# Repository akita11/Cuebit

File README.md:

# Cue:bit

ライントレースと3色のカラーマーカでの動作制御ができるプログラミング教材ロボットカーです。micro:bitを装着して、micro:bitのカスタムブロックで動作制御することもできます。

[使い方・動作の例(YouTube動画)](https://youtu.be/czKjS_mCOlM)

## 使い方（ライントレースモード）

電源を入れると、ライントレースを開始します。また途中にカラーマーカーがあると、それに応じた動作をします。なおライン（黒）やカラーマーカを見失って0,5秒程度経過すると、自動的に停止します（本体LEDが黄色点灯）。ラインやマーカのあるところに移動させると、動作を再開します。

### カラーマーカーと動作の定義

赤・緑・黄の3色のマーカを3つ連続して配置されたところを通過すると、その色パターンに応じた動作を行います。色マーカは10mm程度の「丸ポチシール」（DAISOなどで売っているもの）や、同等の色を印刷したものを使います。(赤=R／緑=G／黄=Y）

- 緑-赤-黄 (GRY) : 速度を超ゆっくりに
- 赤-緑-黄 (RGY) : 速度をゆっくりに
- 赤-緑-赤 (RGR) : 速度を通常に
- 黄-緑-赤 (YGR) : 速度を速く
- 黄-赤-緑 (YRG) : 速度を超速く
- 黄-赤-黄 (YRY) : 一時停止（3秒程度）
- 緑-黄-赤 (GYR) : 次の交差点を左に90度曲がる
- 黄-緑-黄 (YGY) : 次の交差点を直進する
- 緑-黄-緑 (GYG) : 次の交差点を右に90度曲がる
- 赤-黄-赤 (RYR) : Uターンする
- 緑-赤-緑 (GRG) : バックする

## 使い方（micro:bitモード）

micro:bitのカスタムブロックを使ってCue:bitの動作を制御でききます。
[こちらの手順](https://docs.google.com/document/d/1bRiQpdVX2RdSoQZLEZQx14lWcuVc2Sd8CT0sPL3RYwU/)でMakeCode用カスタムブロックを追加し、micro:bitのプログラムを作成してmicro:bitに書き込みます。その後、そのmicro:bitをCue:bitに差し込んでCue:bitの電源をいれると、そのプログラム通りにCue:bitが動作します。

※モータの特性仕様上、左右の回転速度には差があり、以下のコマンドである程度は調整はできますが、完全に直進したり正確に指定距離だけ進む・回転することはできません。ご了承ください。

### 参考：技術的仕様

micro:bitからCue:bitへのコマンド（通信プロトコル:UART 9600bps N81）は以下です。以下の"NNN"は数値(10進数)で与えるコマンドパラメータです。また各コマンドは行末コード(0x0d or 0x0a)で終端します。なおCue:bitのGroveコネクタと本体後部の6ピンコネクタ用端子(FTDI-Basic用)も、micro:bitの通信端子と並列に接続されています。なお[「Groveケーブル-USBシリアル接続ケーブル」](https://www.switch-science.com/products/9460)を使うと、FTDI-Basicと本体Grove端子とを接続できます。なおソースコードはArduinoIDE等で書き込むことができます。（ターゲットはProMini(ATmega328P, 3.3V/8MHz)。新品ATmega328Pではこれ用のブートローダを書き込む必要あり）

- $ : micro:bit制御モードに開始
- \# : micro:bit制御モードを終了
- RNNN : NNN度回転（NNNが正=時計回り、負=反時計回り）（※実際の回転角度はモータ特性のばらつきなどから多少の誤差があります）
- B : 停止
- FNNN : NNN[cm]進む（※実際の移動距離はモータ特性のばらつきなどから多少の誤差があります）
- ZNNN : ジグザグ走行（およそNNN[cm]）
- SNNN : スケート走行（およそNNN[cm]）

以下はデバッグ用のコマンド

- P : パラメータの表示
- T : ライントレースモードを開始
- t : ライントレースモードを終了して停止
- D : デバッグ情報の表示を開始（Dに続けてr/g/y/wを書くと、色センサの値を各色の学習用のCSV形式で出力）
- d : デバッグ表示の表示を停止
- kNNN : ライントレース制御のKpパラメータ（float型）
- KNNN : ライントレース制御のKdパラメータ（float型）
- vNNN : 通常走行時の速度（float型。モータ駆動のPWM比として与えるため、値の範囲は0.0〜1.0）
- rNNN : 左右モータの速度調整（PWMデューティー比）（float型）（左モータのPWM比×r=右モータのPWM比として計算するため、v×rが1.0以下となること）
- fNNN : 1cm進むための時間[単位は10ms]（※実際の移動距離はモータ特性のばらつきなどから多少の誤差があります）
- gNNN : 10度回転するための時間[単位は10ms]（※実際の回転角度はモータ特性のばらつきなどから多少の誤差があります）
- ! : 各種パラメータをEEPROMに保存（起動時に読み込まれる）

## Author

Junichi Akita (@akita11) / akita@ifdl.jp

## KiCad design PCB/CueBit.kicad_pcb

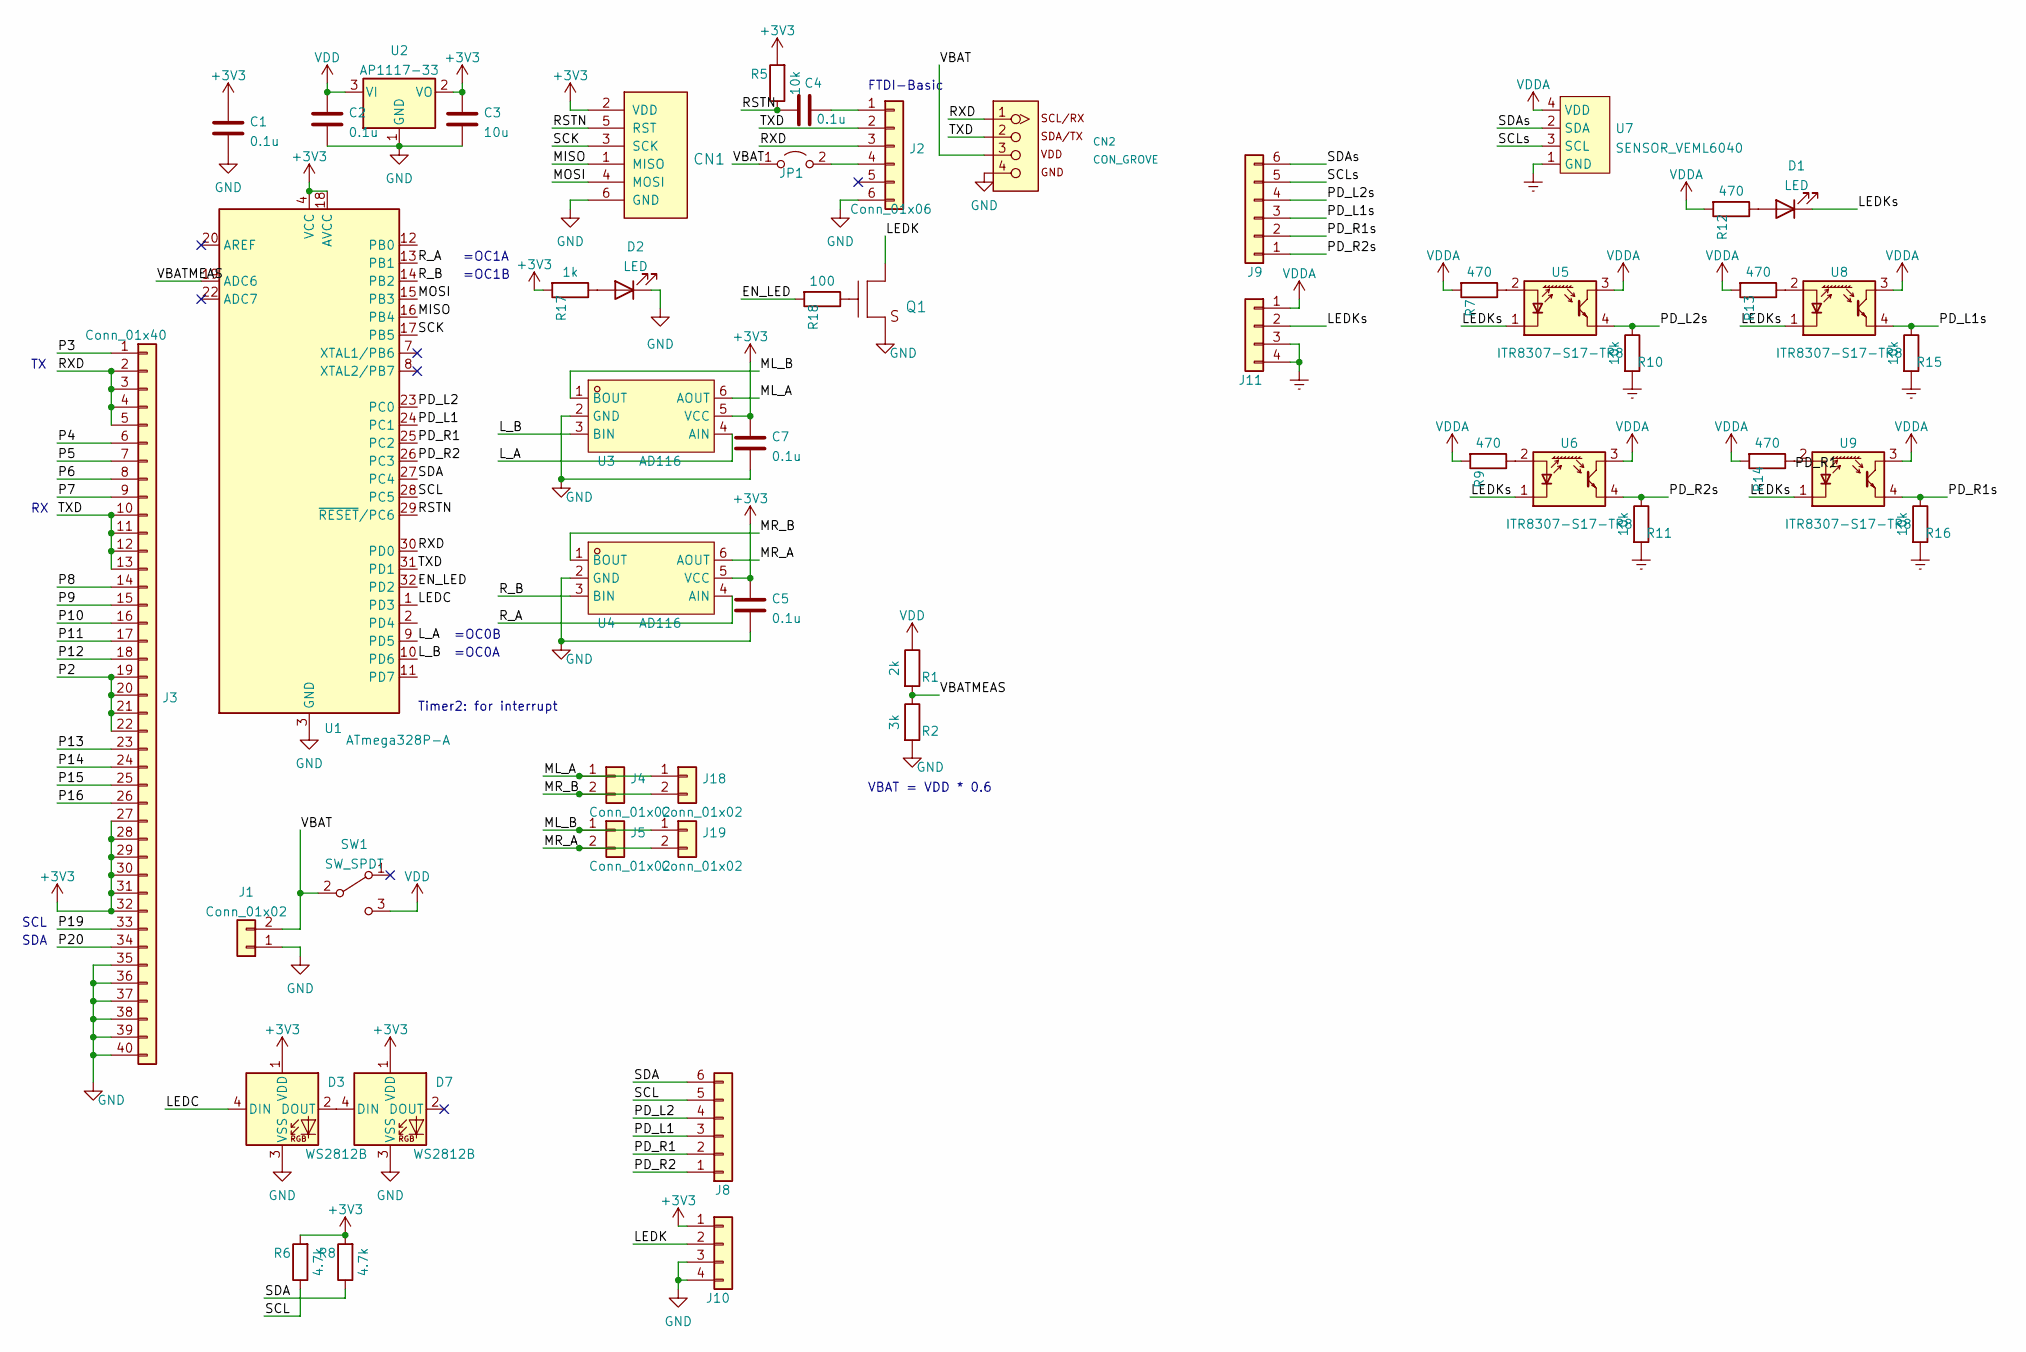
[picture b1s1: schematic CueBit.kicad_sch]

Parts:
C1, C2, C4, C5, C7: 0.1u; C_0603_1608Metric
C3: 10u; C_0603_1608Metric
CN1: CON_AVRISP; PinHeader_2x03_P2.54mm_Vertical
CN2: CON_GROVE; CON_GROVE_H_roundPad
D1, D2: LED; LED_0603_1608Metric
D3, D7: WS2812B; LED_WS2812B_PLCC4_5.0x5.0mm_P3.2mm
J1: Conn_01x02; JST_PH_B2B-PH-K_1x02_P2.00mm_Vertical
J2: Conn_01x06; PinSocket_1x06_P2.54mm_Vertical
J3: Conn_01x40; CON_microbit_cardedge_V_SMD
J4, J5: Conn_01x02; PinHeader_1x02_P2.54mm_Vertical
J8, J9: Conn_01x06; PinHeader_1x06_P2.54mm_Vertical
J10, J11: Conn_01x04; PinSocket_1x04_P2.54mm_Vertical
J18, J19: Conn_01x02; PinHeader_1x02_P2.54mm_Vertical_SMD_Pin1Right
JP1: Jumper_2_Open; SolderJumper-2_P1.3mm_Open_Pad1.0x1.5mm
Q1: TR_NMOS_IRLML6344; SOT-23
R1: 2k; R_0603_1608Metric; LCSC C2907022
R2: 3k; R_0603_1608Metric; LCSC C328357
R5, R10, R11, R15, R16: 10k; R_0603_1608Metric
R6, R8: 4.7k; R_0603_1608Metric
R7, R9, R12, R13, R14: 470; R_0603_1608Metric; LCSC C2907172
R17: 1k; R_0603_1608Metric
R18: 100; R_0603_1608Metric
SW1: SW_SPDT; SW_SK-12D11VG3
U1: ATmega328P-A; TQFP-32_7x7mm_P0.8mm; LCSC C14877
U2: AP1117-33; SOT-223-3_TabPin2; LCSC C2992570
U3, U4: AD116; SOT-23-6_L2.9-W1.6-P0.95-LS2.8-BL; LCSC Part C7463412
U5, U6, U8, U9: ITR8307-S17-TR8; Everlight_ITR1201SR10AR; LCSC C81632
U7: SENSOR_VEML6040; OPLGA-4; LCSC C78465

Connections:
+3V3: C1.1, C3.1, C5.1, C7.1, CN1.2 (VDD), D3.1 (VDD), D7.1 (VDD), J3.27, J3.28, J3.29, J3.30, J3.31, J3.32, J10.1, R5.2, R6.2, R8.2, R17.2, U1.4 (VCC), U1.6 (VCC), U1.18 (AVCC), U2.2 (VO), U3.5 (VCC), U4.5 (VCC)
/EN_LED: R18.2, U1.32 (PD2)
/LEDC: D3.4 (DIN), U1.1 (PD3)
/LEDK: J10.2, Q1.3 (D)
/LEDKs: D1.1 (K), J11.2, U5.1 (K), U6.1 (K), U8.1 (K), U9.1 (K)
/L_A: U1.9 (PD5), U3.4 (AIN)
/L_B: U1.10 (PD6), U3.3 (BIN)
/MISO: CN1.1 (MISO), U1.16 (PB4)
/ML_A: J4.1, J18.1, U3.6 (AOUT)
/ML_B: J5.1, J19.1, U3.1 (BOUT)
/MOSI: CN1.4 (MOSI), U1.15 (PB3)
/MR_A: J5.2, J19.2, U4.6 (AOUT)
/MR_B: J4.2, J18.2, U4.1 (BOUT)
/P2: J3.19, J3.20, J3.21, J3.22
/P3: J3.1
/P4: J3.6
/P5: J3.7
/P6: J3.8
/P7: J3.9
/P8: J3.14
/P9: J3.15
/P10: J3.16
/P11: J3.17
/P12: J3.18
/P13: J3.23
/P14: J3.24
/P15: J3.25
/P16: J3.26
/P19: J3.33
/P20: J3.34
/PD_L1: J8.3, U1.24 (PC1)
/PD_L1s: J9.3, R15.1, U8.4
/PD_L2: J8.4, U1.23 (PC0)
/PD_L2s: J9.4, R10.1, U5.4
/PD_R1: J8.2, U1.25 (PC2)
/PD_R1s: J9.2, R16.1, U9.4
/PD_R2: J8.1, U1.26 (PC3)
/PD_R2s: J9.1, R11.1, U6.4
/RSTN: C4.1, CN1.5 (RST), R5.1, U1.29 (~RESET/PC6)
/RXD: CN2.1, J2.3, J3.2, J3.3, J3.4, J3.5, U1.30 (PD0)
/R_A: U1.13 (PB1), U4.4 (AIN)
/R_B: U1.14 (PB2), U4.3 (BIN)
/SCK: CN1.3 (SCK), U1.17 (PB5)
/SCL: J8.5, R6.1, U1.28 (PC5)
/SCLs: J9.5, U7.3 (SCL)
/SDA: J8.6, R8.1, U1.27 (PC4)
/SDAs: J9.6, U7.2 (SDA)
/TXD: CN2.2, J2.2, J3.10, J3.11, J3.12, J3.13, U1.31 (PD1)
/VBAT: CN2.3, J1.2, JP1.1 (A), SW1.2 (B)
/VBATMEAS: R1.2, R2.1, U1.19 (ADC6)
Earth: J11.3, J11.4, R10.2, R11.2, R15.2, R16.2, U7.1 (GND)
GND: C1.2, C2.2, C3.2, C5.2, C7.2, CN1.6 (GND), CN2.4, D2.1 (K), D3.3 (VSS), D7.3 (VSS), J1.1, J2.6, J3.35, J3.36, J3.37, J3.38, J3.39, J3.40, J10.3, J10.4, Q1.2 (S), R2.2, U1.3 (GND), U1.5 (GND), U1.21 (GND), U2.1 (GND), U3.2 (GND), U4.2 (GND)
unnamed: C4.2, J2.1
unnamed: D1.2 (A), R12.1
unnamed: D2.2 (A), R17.1
unnamed: D3.2 (DOUT), D7.4 (DIN)
unnamed: J2.4, JP1.2 (B)
unnamed: Q1.1 (G), R18.1
unnamed: R7.1, U5.2 (A)
unnamed: R9.1, U6.2 (A)
unnamed: R13.1, U8.2 (A)
unnamed: R14.1, U9.2 (A)
VDD: C2.1, R1.1, SW1.3 (C), U2.3 (VI)
VDDA: J11.1, R7.2, R9.2, R12.2, R13.2, R14.2, U5.3, U6.3, U7.4 (VDD), U8.3, U9.3

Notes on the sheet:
SDA
VBAT = VDD * 0.6
Timer2: for interrupt
FTDI-Basic
=OC1A
=OC1B
=OC0B
=OC0A
SCL

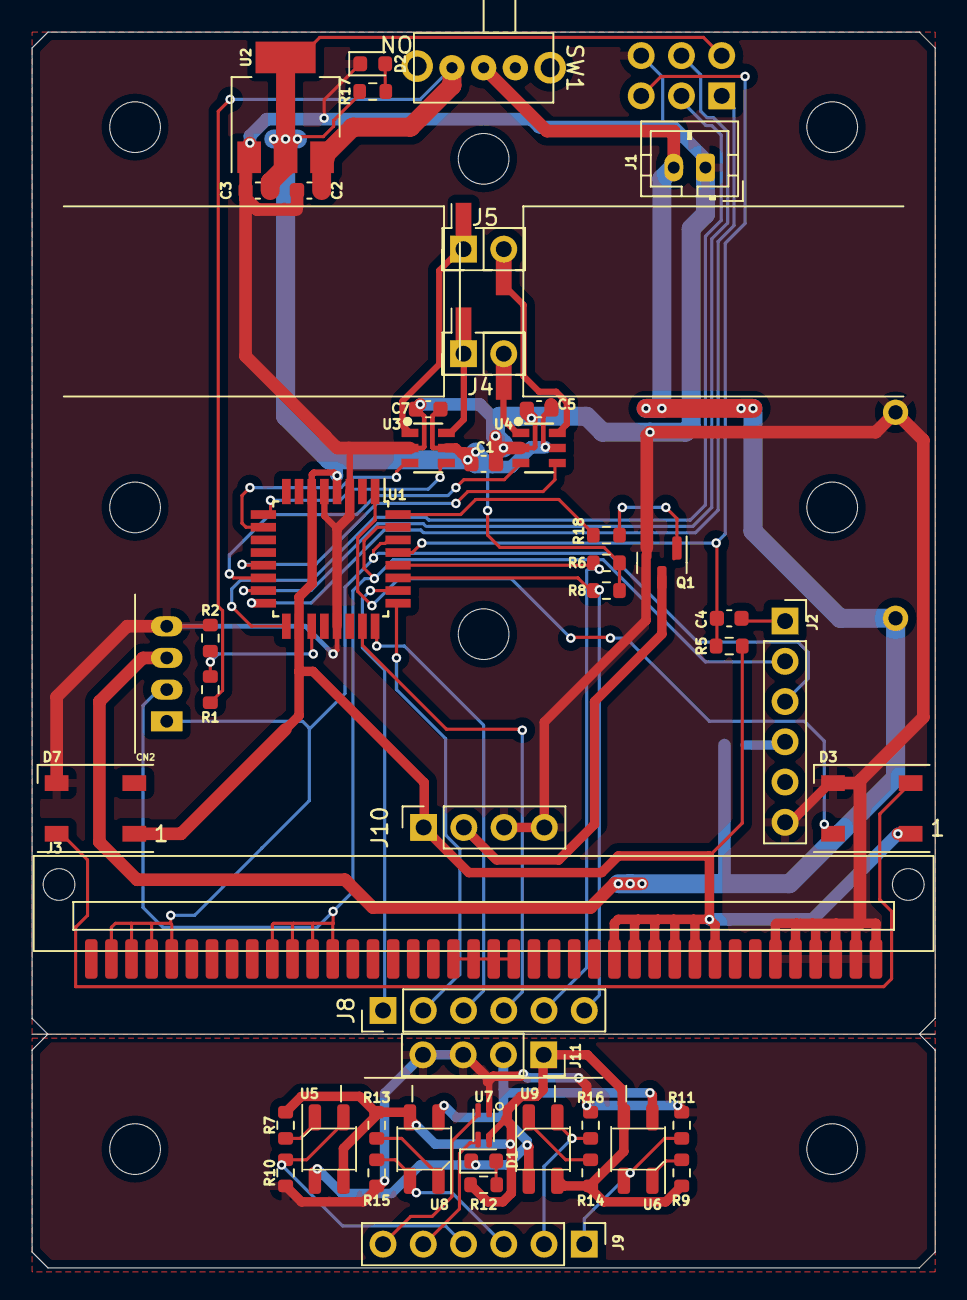
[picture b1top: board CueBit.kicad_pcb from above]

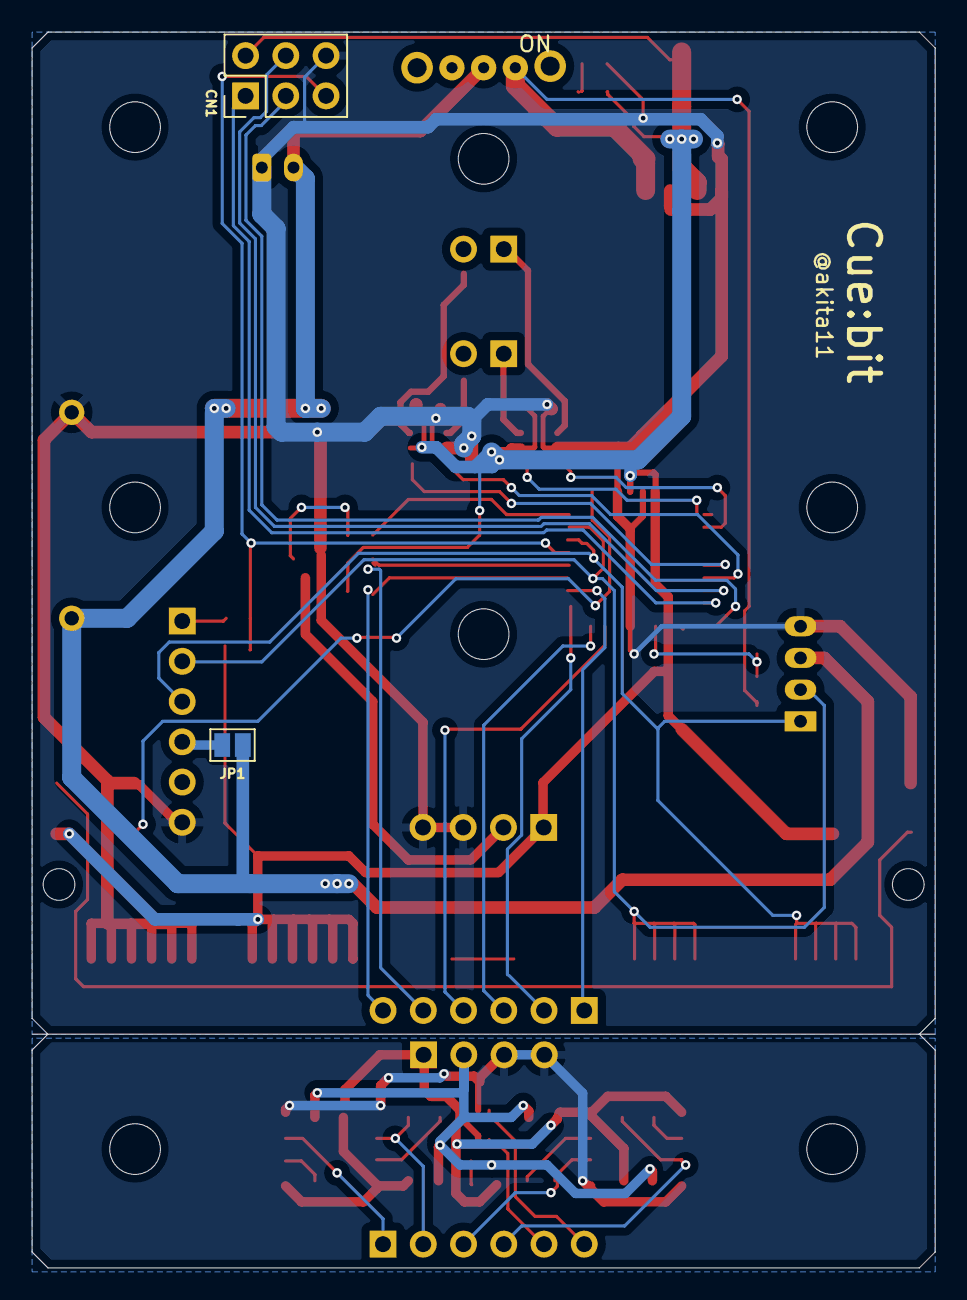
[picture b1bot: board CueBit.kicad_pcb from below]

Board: 2 copper layers, 57.0 x 78.0 mm, 51 parts (2 on the bottom side), 48 nets.

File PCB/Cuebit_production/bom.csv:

Designator,Footprint,Quantity,Value,LCSC Part #
"C1, C2, C4, C5, C7",C_0603_1608Metric,5,0.1u,C14663
C3,C_0603_1608Metric,1,10u,C109454
D1,LED_0603_1608Metric,2,LED(W),C7371902
D2,,,LED(G),C165982
"D3, D7",LED_WS2812B_PLCC4_5.0x5.0mm_P3.2mm,2,WS2812B,C22461793
Q1,SOT-23,1,TR_NMOS_IRLML6344,C20917
"R10, R11, R15, R16, R5",R_0603_1608Metric,5,10k,C25804
"R12, R13, R14, R7, R9",R_0603_1608Metric,5,470,C2907172
R17,R_0603_1608Metric,1,1k,C21190
R18,R_0603_1608Metric,1,100,C103204
"R6, R8",R_0603_1608Metric,2,4.7k,C103656
U1,TQFP-32_7x7mm_P0.8mm,1,ATmega328P-A,C14877
U2,SOT-223-3_TabPin2,1,AP1117-33,C2763399
"U3, U4",SOT-23-6_L2.9-W1.6-P0.95-LS2.8-BL,2,AD116,C2845121
"U5, U6, U8, U9",Everlight_ITR1201SR10AR,4,ITR8307-S17-TR8,C81632
U7,OPLGA-4,1,SENSOR_VEML6040,C78465
R1,R_0603_1608Metric,1,200k,C2907122
R2,R_0603_1608Metric,1,300k,C23024

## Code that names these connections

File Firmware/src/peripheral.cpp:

#include <Arduino.h>
#include "Wire.h"
#include "veml6040.h"
#include <Adafruit_NeoPixel.h>

#include "peripheral.h"

// https://github.com/thewknd/VEML6040/
VEML6040 RGBWSensor;

#define R_B    5 // PD5
#define R_A    6 // PD6
#define L_A    9 // PB1
#define L_B    10 // PB2
#define LEDC   3 // for WS2812
#define LED_EN 2 // PD2
#define PD_R2  A3
#define PD_R1  A2
#define PD_L1  A1
#define PD_L2  A0

// for wide sensor
#define BLACK_PD_R2 36
#define WHITE_PD_R2 360
#define BLACK_PD_R1 42
#define WHITE_PD_R1 342
#define BLACK_PD_L1 45
#define WHITE_PD_L1 400
#define BLACK_PD_L2 35
#define WHITE_PD_L2 350
#define BLACK_COLOR 11000
#define WHITE_COLOR 20000

#define MAX_PWM_L 255
#define MAX_PWM_R 255

Adafruit_NeoPixel pixel(2, LEDC, NEO_GRB + NEO_KHZ800);

void init_peripheral()
{
  pixel.begin(); pixel.clear();
	pinMode(LED_EN, OUTPUT);
	setLED(20, 0, 0);
	setMotorSpeed(0.0, 0.0);
	enableSensorLED(0);
  Wire.begin(); 
	RGBWSensor.setConfiguration(VEML6040_IT_40MS + VEML6040_AF_AUTO + VEML6040_SD_ENABLE);
  if(!RGBWSensor.begin()) {
    Serial.println("VEML6040 init error");
    while(1){ setLED(20, 0, 0); delay(100); setLED(0, 0, 0); delay(100); }
  }
}

void enableSensorLED(uint8_t f)
{
	if (f == 1) digitalWrite(LED_EN, HIGH);
	else digitalWrite(LED_EN, LOW);
}

uint16_t convMotorPWM(uint8_t max_pwm, float v){
	if (v > 1.0) return(max_pwm);
	else return((uint16_t)(max_pwm * v));
}

// vL/vR : -1 - +1 / +=FWD, -=BWD
void setMotorSpeed(float vL, float vR)
{
	if (vL > 0){
		analogWrite(L_A, convMotorPWM(MAX_PWM_L, vL));	analogWrite(L_B, 0);
	}
	else{
		analogWrite(L_A, 0); analogWrite(L_B, -convMotorPWM(MAX_PWM_L, vL));
	}
	if (vR > 0){
		analogWrite(R_A, convMotorPWM(MAX_PWM_R, vR * LRratio));	analogWrite(R_B, 0);
	}
	else{
		analogWrite(R_A, 0); analogWrite(R_B, -convMotorPWM(MAX_PWM_R, vR * LRratio));
	}
}

void setLED(uint8_t r, uint8_t g, uint8_t b)
{
	pixel.setPixelColor(0,  pixel.Color(r, g, b)); pixel.setPixelColor(1,  pixel.Color(r, g, b)); pixel.show();
}

uint8_t classify(float R, float G, float B, float W) {
	/*
	float weights[5][5] = {
		{-0.215193,  0.158631,  0.447248,  0.000700, -24.586008},
		{-0.478091, -0.265669,  0.986931, -0.001539,  21.651707},
		{ 0.355452, -0.928157, -0.255726,  0.000547,  32.428762},
		{-0.102398,  0.391205, -0.465644, -0.000426,  10.497819},
		{ 0.440230,  0.643990, -0.712809,  0.000718, -39.992280}
	};
	*/
	// data in 251211
	float weights[5][5] = {
	  {-0.511273, 0.538672, 0.358886, 0.000558, -26.676748},
  	{-0.172642, -0.442766, 0.599960, -0.001610, 35.171817},
  	{0.912427, -0.697076, -0.323679, 0.000352, -1.350221},
  	{-0.687868, 0.318697, -0.092341, 0.000292, 19.035786},
  	{0.459356, 0.282473, -0.542826, 0.000408, -26.180634}
	};
	float input[4] = {R, G, B, W};
	float scores[5];

	for (int c = 0; c < 5; c++) {
		scores[c] = weights[c][4]; // bias
		for (int i = 0; i < 4; i++) {
			scores[c] += input[i] * weights[c][i];
		}
	}

	int maxIndex = 0;
	for (int c = 1; c < 5; c++) {
		if (scores[c] > scores[maxIndex]) {
			maxIndex = c;
		}
	}

	if (maxIndex == 0) return(COLOR_WHITE);
	else if (maxIndex == 1) return(COLOR_BLACK);
	else if (maxIndex == 2) return(COLOR_RED);
	else if (maxIndex == 3) return(COLOR_GREEN);
	else return(COLOR_BLUE);
}

// BLACK(1.0) - WHITE(0.0)
float lineValue(uint16_t val, uint16_t vBlack, uint16_t vWhite){
	float v;
	if (val < vBlack) v = 1.0;
	else if (val > vWhite) v = 0.0;
	else v = (float)(vWhite - val) / (float)(vWhite - vBlack);
	return(v);
}

SensorData readSensor(SensorData sd)
{
	// return: L2:L1:C:R1:R2:{COLOR[2:0]} (1=line detected)
	uint8_t sensorInfo = COLOR_NONE;
	uint16_t sensorR, sensorG, sensorB, sensorW;

	enableSensorLED(1);
//	delay(2);

	float s = 0.0;
	float v;
	sd.line = 0.0;
	v = lineValue(analogRead(PD_L2), BLACK_PD_L2, WHITE_PD_L2); sd.line += v * (-2); s += v;
	v = lineValue(analogRead(PD_L1), BLACK_PD_L1, WHITE_PD_L1); sd.line += v * (-1); s += v;
	v = lineValue(analogRead(PD_R1), BLACK_PD_R1, WHITE_PD_R1); sd.line += v * (+1); s += v;
	v = lineValue(analogRead(PD_R2), BLACK_PD_R2, WHITE_PD_R2); sd.line += v * (+2); s += v;

	sensorR = RGBWSensor.getRed();
	sensorG = RGBWSensor.getGreen();
	sensorB = RGBWSensor.getBlue();
	sensorW = RGBWSensor.getWhite();
//	enableSensorLED(0);

	// normalize
	float sensorRf, sensorGf, sensorBf;
	sensorRf = (float)sensorR / (float)sensorW * 100.0;
	sensorGf = (float)sensorG / (float)sensorW * 100.0;
	sensorBf = (float)sensorB / (float)sensorW * 100.0;

/*
	if (sensorW > WHITE_COLOR) sensorInfo = COLOR_WHITE;
	else sensorInfo = classify(sensorRf, sensorGf, sensorBf, sensorW);
*/
	sensorInfo = classify(sensorRf, sensorGf, sensorBf, sensorW); // model including W 
	sd.color = sensorInfo;
	if (stLEDmsg == LEDMSG_NONE){
		if (sensorInfo == COLOR_BLACK) setLED(0, 0, 0);
		else if (sensorInfo == COLOR_RED) setLED(10, 0, 0);
		else if (sensorInfo == COLOR_GREEN) setLED(0, 10, 0);
//		else if (sensorInfo == COLOR_BLUE) setLED(0, 0, 10); // blue (old)
		else if (sensorInfo == COLOR_BLUE) setLED(6, 6, 0); // yellow
		else if (sensorInfo == COLOR_WHITE) setLED(10, 10, 10);
	}
	
	if (sensorInfo != COLOR_WHITE) s += lineValue(sensorW, BLACK_COLOR, WHITE_COLOR);	
//	if (s == 0.0) sd.line = -10.0;
	if (s <  0.3) sd.line = -10.0;
	else sd.line = sd.line / s;
	sd.width = s;
	if (fDebug > 0){
	 	Serial.print(sensorRf); Serial.print(",");
	 	Serial.print(sensorGf); Serial.print(",");
	 	Serial.print(sensorBf); Serial.print(",");
	 	Serial.print(sensorW); Serial.print(",");
		if (fDebug == 6){
	 		Serial.print("|,");
		 	Serial.print(analogRead(PD_R2)); Serial.print(',');
		 	Serial.print(analogRead(PD_R1)); Serial.print(',');
	 		Serial.print(analogRead(PD_L1)); Serial.print(',');
	 		Serial.print(analogRead(PD_L2)); Serial.print(",|,");
			Serial.print(lineValue(analogRead(PD_R2), BLACK_PD_R2, WHITE_PD_R2)); Serial.print(',');
			Serial.print(lineValue(analogRead(PD_R1), BLACK_PD_R1, WHITE_PD_R1)); Serial.print(',');
			Serial.print(lineValue(analogRead(PD_L1), BLACK_PD_L1, WHITE_PD_L1)); Serial.print(',');
			Serial.print(lineValue(analogRead(PD_L2), BLACK_PD_L2, WHITE_PD_L2)); Serial.print(',');
			if (sensorInfo != COLOR_WHITE) Serial.print(lineValue(sensorW, BLACK_COLOR, WHITE_COLOR));
			Serial.print(",|,"); Serial.print(sd.line);
			Serial.print(','); Serial.print(sd.width);
			Serial.print('/'); Serial.print(sd.color);
//			Serial.print('|'); Serial.print(vL); Serial.print(','); Serial.println(vR);
			Serial.print(','); Serial.print(BatteryVoltage);
			Serial.println("");
		}
		else if (fDebug >= 1 && fDebug <= 5) Serial.println(fDebug); // with color label
	}
	return(sd);
}

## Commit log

2024-07-28 working
2024-07-28 functions for motors & sensors
2024-08-01 component test
2024-08-01 read line define
2024-08-02 sensor calibration
2024-08-02 motor control
2024-08-13 tentative working
2024-08-27 for DC motor
2024-09-29 tentative line trace
2024-10-03 analog lineValue
2024-10-08 analog line trace
2024-10-23 serial debug
2024-10-29 color classify
2024-10-29 tentative UART commands
2024-10-30 color detection tuning
2024-11-07 color command (not full)
2024-11-08 skip cross
2024-11-08 9600bps
2024-11-10 refactoring
2024-11-21 refactoring & timer ISR motion control
2024-11-22 enable sensor LED_EN as output
2024-12-16 param for wide sensor board
2024-12-16 tentative skate&zigzag
2024-12-17 color sensor black detection
2024-12-18 comands implemented
2024-12-19 command implementation
2024-12-19 color adjustment
2024-12-20 tentative for motion at cross
2024-12-21 go after cross
2024-12-24 after cross turn
2025-01-07 parameter save
2025-01-07 color model improve
2025-02-21 model improve, color logging cmd
2025-03-07 low battery detection
2025-03-18 color model for yellow, stop at white
2025-03-27 stop at line lost, parameter save,
2025-03-27 parameters for production model
2025-03-28 add README
2025-04-05 color model & train py
2025-04-05 modified .gitignore
2025-04-09 LED blink debug
2025-05-01 change skate&zigzap parameter
2025-12-10 color coeff update, supress debug msg during logging
2025-12-11 add color_train_eval.py, stop motors during color logging
